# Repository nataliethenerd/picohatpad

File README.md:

# Pico Hat Pad
A Raspberry Pi Pico hat with two mechanical switches and a rotary encoder. Powered by KMK

This kit aims to be a cheap (under $20aud including caps, keys, pico, pcbs, head pins) macro pad and solder practice kit

# BOM
2 X 20 stacked header pins

2 X keyboard switches

2 X WS2812B

1 X EC11 encoder

1 X Raspberry Pi Pico (I used a 1:1 clone that had USB C)

# Guide/Purchase kit

You can by the kit here https://www.nataliethenerd.com/product-page/kit-pico-hat-macro-pad

and an in depth guide can be found here https://www.nataliethenerd.com/picohatmacropad

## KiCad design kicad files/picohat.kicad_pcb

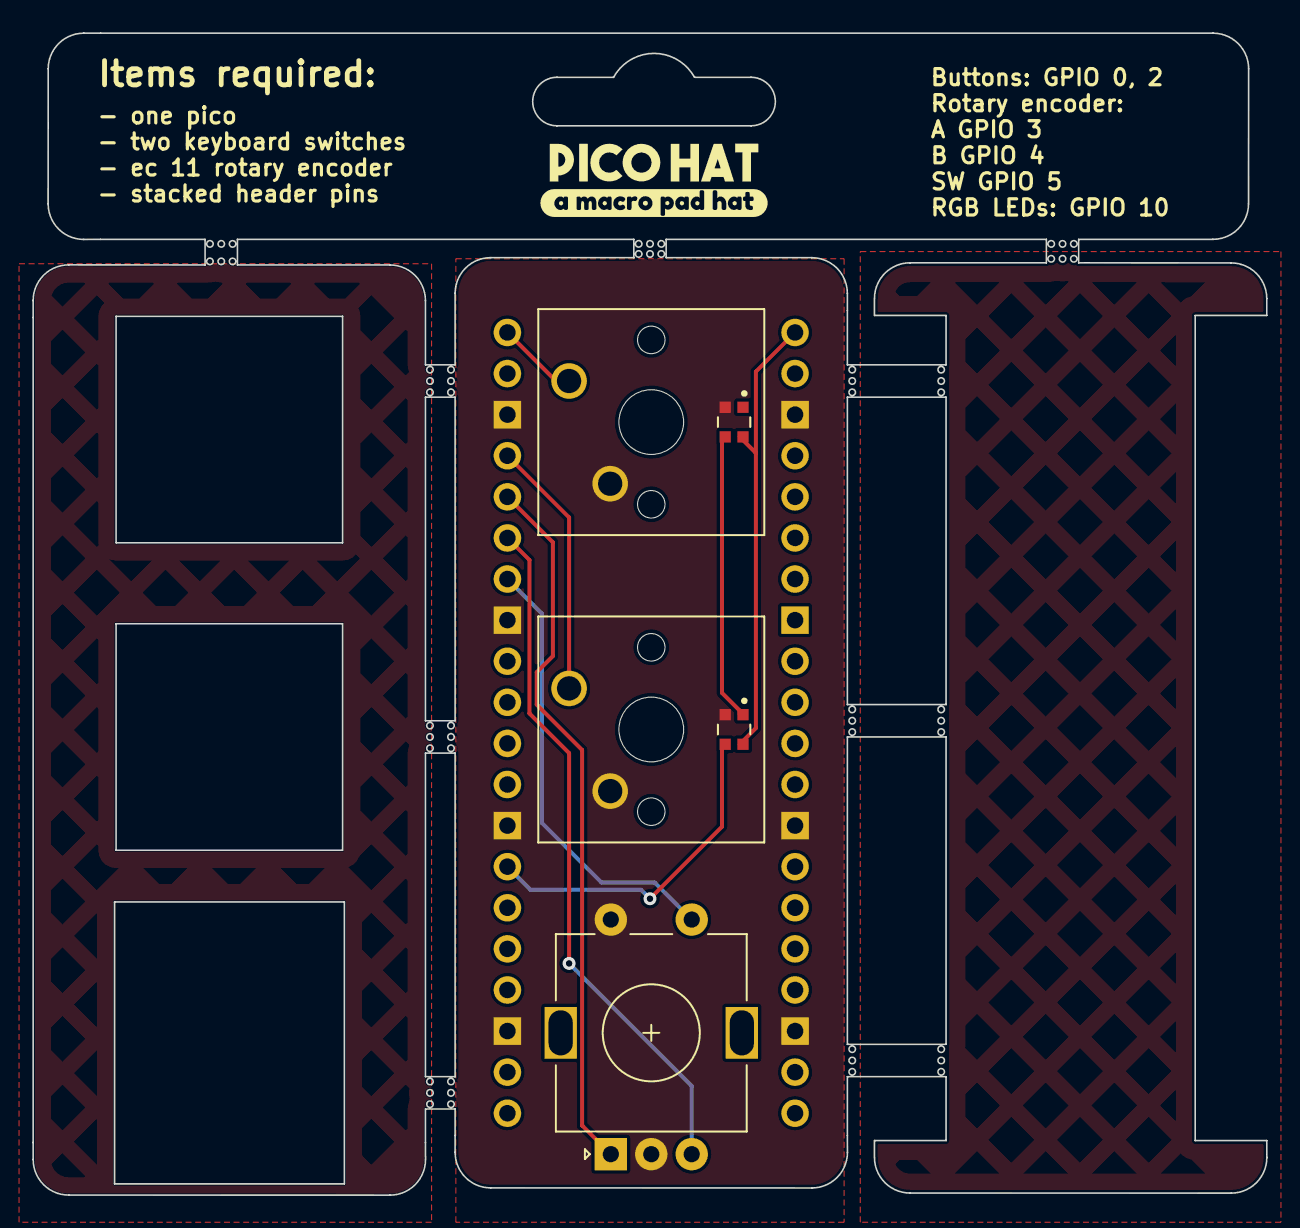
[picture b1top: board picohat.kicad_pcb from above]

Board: 2 copper layers, 76.3 x 71.8 mm, 8 parts (0 on the bottom side), 9 nets.

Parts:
KiFont-63419F7A: G***; KiFont-63419F7A
SW1, SW2: SW_DIP_x01; SW_Cherry_MX_1.00u_PCB
SW3: RotaryEncoder_Switch; RotaryEncoder_Alps_EC11E-Switch_Vertical_H20mm
U1: Pico; RPi_Pico_SMD_TH
U2, U3: WS2812-2020; LED_WS2812-2020
kibuzzard-63419FC0: G***; kibuzzard-63419FC0

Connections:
/GPIO0: SW2.1, U1.1 (GPIO0)
/GPIO2: SW1.1, U1.4 (GPIO2)
/GPIO3: SW3.A, U1.5 (GPIO3)
/GPIO4: SW3.B, U1.6 (GPIO4)
/GPIO5: SW3.S1, U1.7 (GPIO5)
/GPIO10: U1.14 (GPIO10), U2.3 (DI)
/VBUS: U1.40 (VBUS), U2.4 (VDD), U3.4 (VDD)
GND: SW1.2, SW2.2, SW3.C, SW3.S2, U1.3 (GND), U1.8 (GND), U1.13 (GND), U1.18 (GND), U1.23 (GND), U1.28 (GND), U1.38 (GND), U2.2 (GND), U3.2 (GND)
unnamed: U2.1 (DO), U3.3 (DI)

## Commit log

2022-12-19 added libraries
2022-12-19 added pic and lib
2022-12-19 added folders
2022-12-19 added kicad files
2022-12-30 Create LICENCE
